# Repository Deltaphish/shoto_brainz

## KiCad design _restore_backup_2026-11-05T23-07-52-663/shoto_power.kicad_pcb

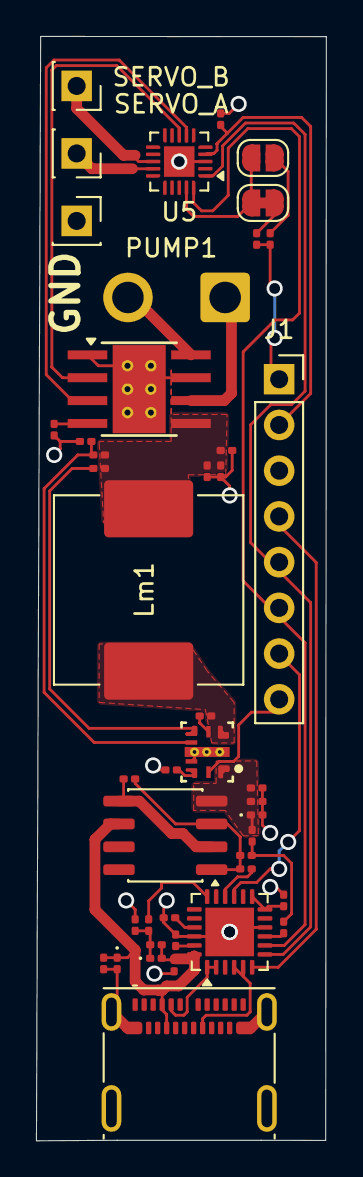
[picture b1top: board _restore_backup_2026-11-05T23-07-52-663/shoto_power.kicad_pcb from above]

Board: 2 copper layers, 16.1 x 61.4 mm, 44 parts (0 on the bottom side), 38 nets.

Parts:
C2: 4.7uf; C_0201_0603Metric
C3, C4, C5, C6: 1uf; C_0201_0603Metric
C7: 100nf; C_0201_0603Metric
C15: 47uF; C_0201_0603Metric
C16, C17: 0.1uF; C_0201_0603Metric
Cm_boot1: 100nF; C_0201_0603Metric
Cm_in1: 4.7uF; C_0201_0603Metric
Cm_inx1: 100nF; C_0201_0603Metric
Cm_out1: 100nF; C_0201_0603Metric
D1: D_Zener; D_0201_0603Metric
D2: VBUS TVS; D_0201_0603Metric
D3: VUSB TVS; D_0201_0603Metric
J1: Conn_01x08_Pin; PinSocket_1x08_P2.54mm_Vertical
J2: USB_C_Receptacle; USB_C_Receptacle_Molex_105450-0101
JP3: SolderJumper_2_Bridged; SolderJumper-2_P1.3mm_Bridged_RoundedPad1.0x1.5mm
JP4: SolderJumper_2_Open; SolderJumper-2_P1.3mm_Open_RoundedPad1.0x1.5mm
Lm1: 3.3uH; L_Vishay_IHLP-4040
PUMP1: Conn_01x02_Socket; SolderWire-1sqmm_1x02_P5.4mm_D1.4mm_OD2.7mm
Q3: Q_Dual_PMOS_G1S2G2D2S1D1; SO-8_3.9x4.9mm_P1.27mm
R3, R8, R20: 1k; R_0201_0603Metric
R4: 470; R_0201_0603Metric
R5, R9, R10: 100k; R_0201_0603Metric
R6: 22k; R_0201_0603Metric
R7: 100; R_0201_0603Metric
R11: 9.09k; R_0201_0603Metric
R18: 32k; R_0201_0603Metric
R19: 4.7k; R_0201_0603Metric
Rm_pg1: 100k; R_0201_0603Metric
Rm_rt1: 15.4k; R_0201_0603Metric
SERVO_A: Conn_01x01_Socket; PinSocket_1x01_P2.54mm_Vertical
SERVO_B: Conn_01x01_Socket; PinSocket_1x01_P2.54mm_Vertical
SERVO_GND1: Conn_01x01_Socket; PinSocket_1x01_P2.54mm_Vertical
U2: STUSB4500QTR; QFN-24-1EP_4x4mm_P0.5mm_EP2.7x2.7mm
U3: PLMR604303SRAKRQ1; RAK0009A-MFG
U5: ATtiny1616-M; VQFN-20-1EP_3x3mm_P0.4mm_EP1.7x1.7mm
U6: DRV8871DDA; Texas_HTSOP-8-1EP_3.9x4.9mm_P1.27mm_EP2.95x4.9mm_Mask2.4x3.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

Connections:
3V3: C17.1, J1.2, U5.4 (VCC)
/Motor Controller/12V: C15.1, C16.1, Cm_out1.2, Lm1.2, R10.1, Rm_pg1.2, U6.5 (VM)
/Motor Controller/M1: PUMP1.1, U6.6 (OUT1)
/Motor Controller/M2: PUMP1.2, U6.8 (OUT2)
/Motor Controller/SERVO_1: SERVO_A.1 (Pin_1_1), U5.14 (PB0)
/Motor Controller/SERVO_2: SERVO_B.1 (Pin_1_1), U5.13 (PB1)
/Motor PSU/VUSB: C7.1, Cm_in1.1, Cm_inx1.1, D3.1 (K), Q3.4 (D), U3.1 (VIN)
/USB PD Controller/CC1: J2.A5 (CC1), U2.1 (CC1DB), U2.2 (CC1)
/USB PD Controller/CC2: J2.B5 (CC2), U2.4 (CC2), U2.5 (CC2DB)
/USB PD Controller/VBUS_IN: C2.1, C6.1, D1.1 (K), D2.2 (A), J2.A4 (VBUS), J2.A9 (VBUS), J2.B4 (VBUS), J2.B9 (VBUS), Q3.6 (D), R4.2, U2.24 (VDD)
GND: C2.2, C3.2, C4.2, C5.2, C6.2, C15.2, C16.2, C17.2, Cm_in1.2, Cm_inx1.2, Cm_out1.1, D1.2 (A), D3.2 (A), J1.3, J2.A1 (GND), J2.A12 (GND), J2.B1 (GND), J2.B12 (GND), J2.SH (SHIELD), R9.2, R11.2, R18.2, Rm_rt1.1, SERVO_GND1.1 (Pin_1_1), U2.10 (GND), U2.22 (VSYS), U2.25 (GND), U3.2 (PGND), U3.7 (MODE_SYNC), U3.10, U3.11, U3.12, U5.3 (GND), U5.21 (GND), U6.1 (GND), U6.7 (GND), U6.9 (GND)
I2C SCL: J1.5, U2.7 (SCL), U5.1 (PA2)
I2C SDA: J1.6, U2.8 (SDA), U5.20 (PA1)
Motor_PSU_Enable: J1.8, U3.9 (EN)
unnamed: C7.2, R7.2, R8.2
unnamed: C3.1, D2.1 (K), R3.2, R4.1
unnamed: JP3.1 (A), JP4.1 (A), U5.19 (~RESET/PA0)
unnamed: JP3.2 (B), R19.1
unnamed: JP4.2 (B), R20.1
unnamed: Q3.1 (G), Q3.3 (G), R5.2, R6.1, R7.1
unnamed: Q3.2 (S), Q3.5 (S), R5.1
unnamed: R9.1, U2.12 (ADDR0), U2.13 (ADDR1)
unnamed: R8.1, U2.9 (DISCH)
unnamed: R6.2, U2.16 (VBUS_EN_SNK)
unnamed: R3.1, U2.18 (VBUS_VS_DISCH)
unnamed: C5.1, U2.21 (VREG_1V2)
unnamed: C4.1, U2.23 (VREG_2V7)
unnamed: Cm_boot1.1, U3.4 (BOOT)
unnamed: R10.2, R11.1, U3.6 (FB)
unnamed: Rm_pg1.1, U3.5 (PG)
unnamed: Rm_rt1.2, U3.8 (RT)
unnamed: Cm_boot1.2, Lm1.1, U3.3 (SW)
unnamed: U5.7 (PA6), U6.3 (IN1)
unnamed: U5.8 (PA7), U6.2 (IN2)
unnamed: R18.1, U6.4 (ILIM)
PROG: J1.1, R19.2, R20.2
USB PD GPIO: J1.7, U2.15 (GPIO)
USB PD RESET: J1.4, U2.6 (RESET)

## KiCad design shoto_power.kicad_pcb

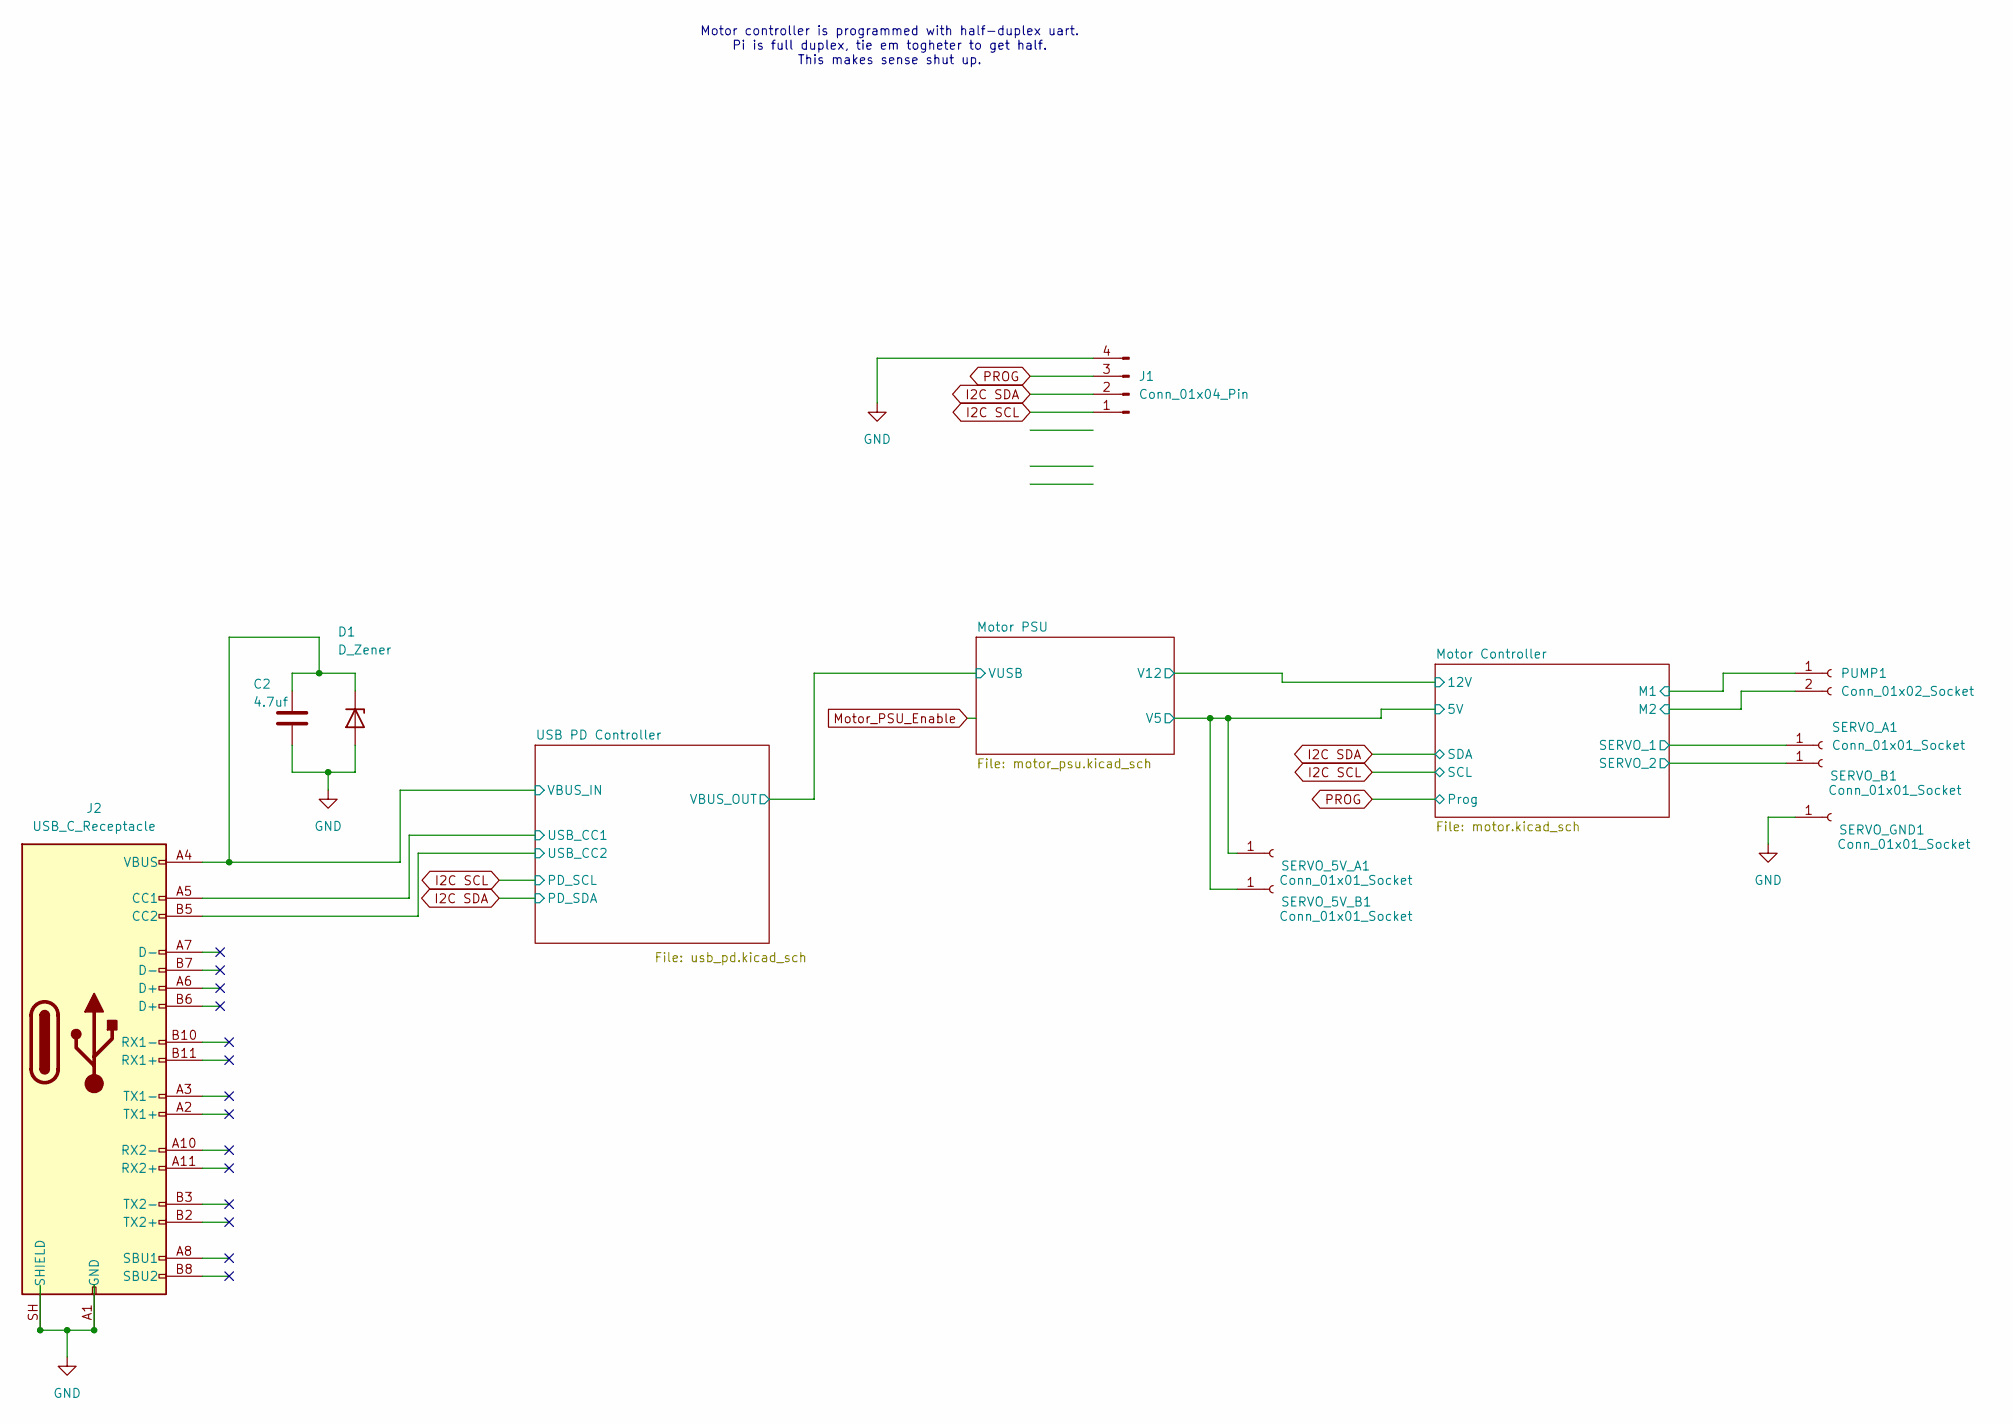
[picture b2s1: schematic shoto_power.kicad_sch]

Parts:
C2: 4.7uf; C_0603_1608Metric
D1: D_Zener; D_0201_0603Metric
J1: Conn_01x04_Pin; PinHeader_1x04_P2.54mm_Vertical
J2: USB_C_Receptacle; USB_C_Receptacle_Molex_105450-0101
PUMP1: Conn_01x02_Socket; SolderWire-1sqmm_1x02_P5.4mm_D1.4mm_OD2.7mm
SERVO_5V_A1, SERVO_5V_B1: Conn_01x01_Socket; PinSocket_1x01_P2.54mm_Vertical
SERVO_A1: Conn_01x01_Socket; PinSocket_1x01_P2.54mm_Vertical
SERVO_B1: Conn_01x01_Socket; PinSocket_1x01_P2.54mm_Vertical
SERVO_GND1: Conn_01x01_Socket; PinSocket_1x01_P2.54mm_Vertical

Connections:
/Motor Controller/5V: SERVO_5V_A1.1 (Pin_1_1), SERVO_5V_B1.1 (Pin_1_1); also elsewhere on the board
/Motor Controller/M1: PUMP1.1; also elsewhere on the board
/Motor Controller/M2: PUMP1.2; also elsewhere on the board
/Motor Controller/T2CH4: SERVO_B1.1 (Pin_1_1); also elsewhere on the board
/Motor PSU/VUSB: C2.1, D1.1 (K), J2.A4 (VBUS), J2.A9 (VBUS), J2.B4 (VBUS), J2.B9 (VBUS); also elsewhere on the board
/USB PD Controller/USB_CC1: J2.A5 (CC1); also elsewhere on the board
/USB PD Controller/USB_CC2: J2.B5 (CC2); also elsewhere on the board
GND: C2.2, D1.2 (A), J1.4, J2.A1 (GND), J2.A12 (GND), J2.B1 (GND), J2.B12 (GND), J2.SH (SHIELD), SERVO_GND1.1 (Pin_1_1); also elsewhere on the board
I2C SCL: J1.1; also elsewhere on the board
I2C SDA: J1.2; also elsewhere on the board
PROG: J1.3; also elsewhere on the board

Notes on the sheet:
Motor controller is programmed with half-duplex uart. Pi is full duplex, tie em togheter to get half. This makes sense shut up.

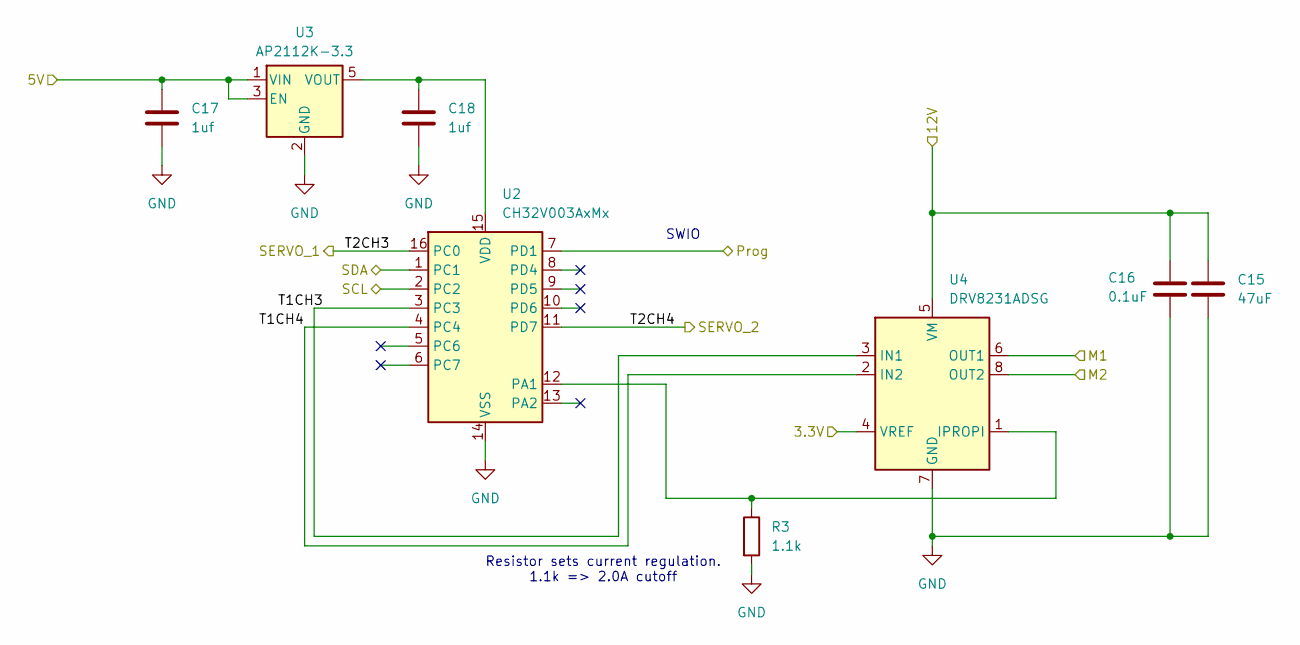
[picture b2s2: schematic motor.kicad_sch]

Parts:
C15: 47uF; C_Elec_6.3x5.4
C16: 0.1uF; C_0201_0603Metric
C17, C18: 1uf; C_0603_1608Metric
R3: 1.1k; R_0805_2012Metric
U2: CH32V003AxMx; STC_SOP-16_3.9x9.9mm_P1.27mm
U3: AP2112K-3.3; SOT-23-5
U4: DRV8231ADSG; Texas_DSG0008A_WSON-8-1EP_2x2mm_P0.5mm_EP0.9x1.6mm

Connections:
/Motor Controller/5V: C17.1, U3.1 (VIN), U3.3 (EN); also elsewhere on the board
/Motor Controller/12V: C15.1, C16.1, U4.5 (VM); also elsewhere on the board
/Motor Controller/M1: U4.6 (OUT1); also elsewhere on the board
/Motor Controller/M2: U4.8 (OUT2); also elsewhere on the board
/Motor Controller/T1CH3: U2.3 (PC3), U4.3 (IN1)
/Motor Controller/T1CH4: U2.4 (PC4), U4.2 (IN2)
/Motor Controller/T2CH3: U2.16 (PC0); also elsewhere on the board
/Motor Controller/T2CH4: U2.11 (PD7); also elsewhere on the board
GND: C15.2, C16.2, C17.2, C18.2, R3.2, U2.14 (VSS), U3.2 (GND), U4.7 (GND), U4.9 (GND); also elsewhere on the board
I2C SCL: U2.2 (PC2); also elsewhere on the board
I2C SDA: U2.1 (PC1); also elsewhere on the board
unnamed: R3.1, U2.12 (PA1), U4.1 (IPROPI)
PROG: U2.7 (PD1); also elsewhere on the board

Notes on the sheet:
Resistor sets current regulation. 1.1k => 2.0A cutoff
SWIO

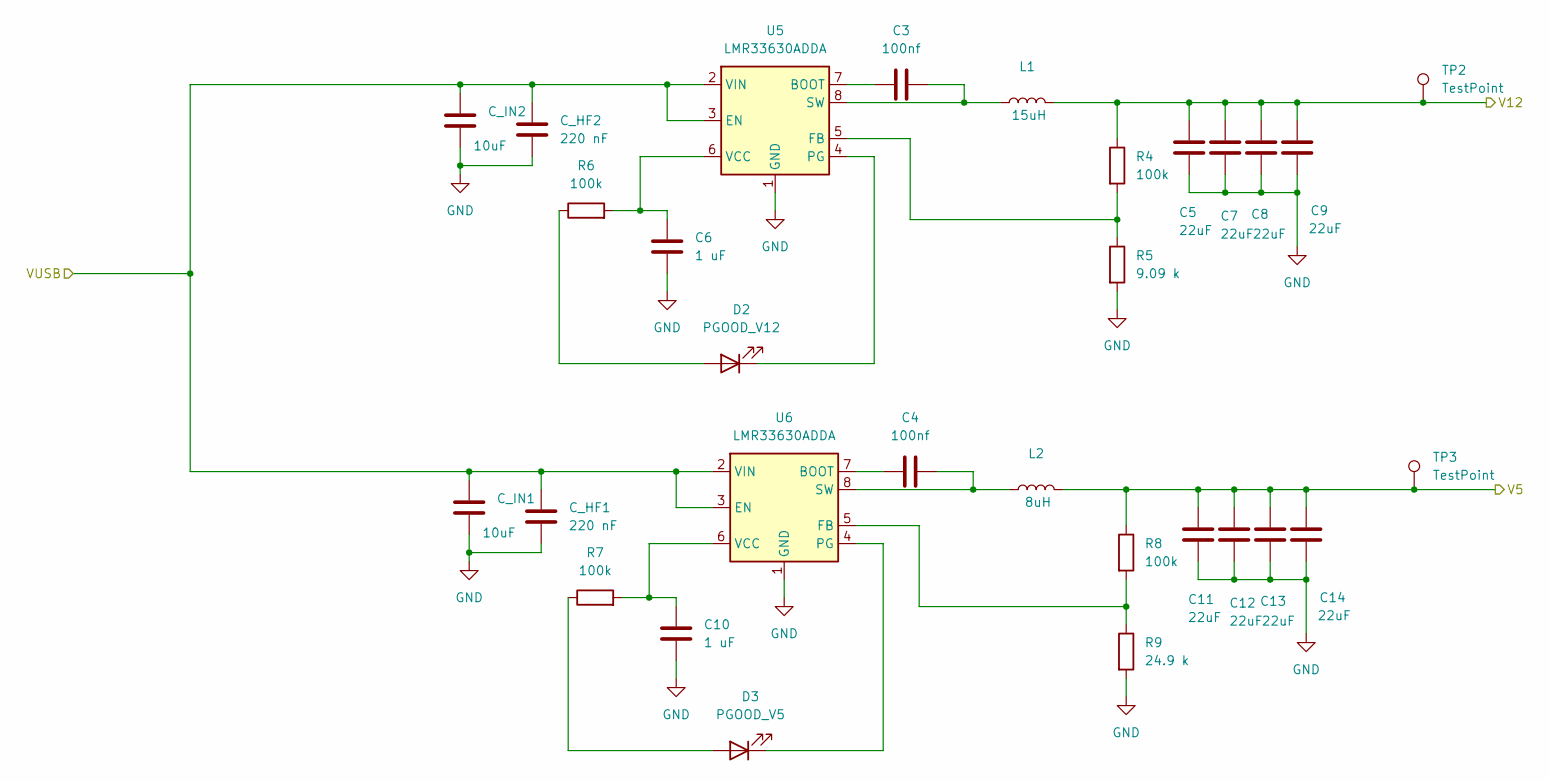
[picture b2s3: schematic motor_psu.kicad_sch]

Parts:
C3, C4: 100nf; C_0603_1608Metric
C5, C7, C8, C9, C11, C12, C13, C14: 22uF; C_1206_3216Metric
C6, C10: 1 uF; C_0603_1608Metric
C_HF1, C_HF2: 220 nF; C_0603_1608Metric
C_IN1, C_IN2: 10uF; C_1206_3216Metric
D2: PGOOD_V12; LED_0603_1608Metric
D3: PGOOD_V5; LED_0603_1608Metric
L1: 15uH; SMDRH104R
L2: 8uH; SER1360
R4, R6, R7, R8: 100k; R_0805_2012Metric
R5: 9.09 k; R_0805_2012Metric
R9: 24.9 k; R_0805_2012Metric
TP2, TP3: TestPoint; TestPoint_Pad_1.5x1.5mm
U5, U6: LMR33630ADDA; Texas_HSOP-8-1EP_3.9x4.9mm_P1.27mm_ThermalVias

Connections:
/Motor Controller/5V: C11.1, C12.1, C13.1, C14.1, L2.2, R8.1, TP3.1; also elsewhere on the board
/Motor Controller/12V: C5.1, C7.1, C8.1, C9.1, L1.2, R4.1, TP2.1 (1_1); also elsewhere on the board
/Motor PSU/VUSB: C_HF1.2, C_HF2.2, C_IN1.2, C_IN2.2, U5.2 (VIN), U5.3 (EN), U6.2 (VIN), U6.3 (EN); also elsewhere on the board
GND: C5.2, C6.2, C7.2, C8.2, C9.2, C10.2, C11.2, C12.2, C13.2, C14.2, C_HF1.1, C_HF2.1, C_IN1.1, C_IN2.1, R5.2, R9.2, U5.1 (GND), U5.9 (GND), U6.1 (GND), U6.9 (GND); also elsewhere on the board
unnamed: D2.2 (A), R6.1
unnamed: D2.1 (K), U5.4 (PG)
unnamed: D3.2 (A), R7.1
unnamed: D3.1 (K), U6.4 (PG)
unnamed: C3.1, U5.7 (BOOT)
unnamed: R4.2, R5.1, U5.5 (FB)
unnamed: C3.2, L1.1, U5.8 (SW)
unnamed: C6.1, R6.2, U5.6 (VCC)
unnamed: C4.1, U6.7 (BOOT)
unnamed: R8.2, R9.1, U6.5 (FB)
unnamed: C4.2, L2.1, U6.8 (SW)
unnamed: C10.1, R7.2, U6.6 (VCC)

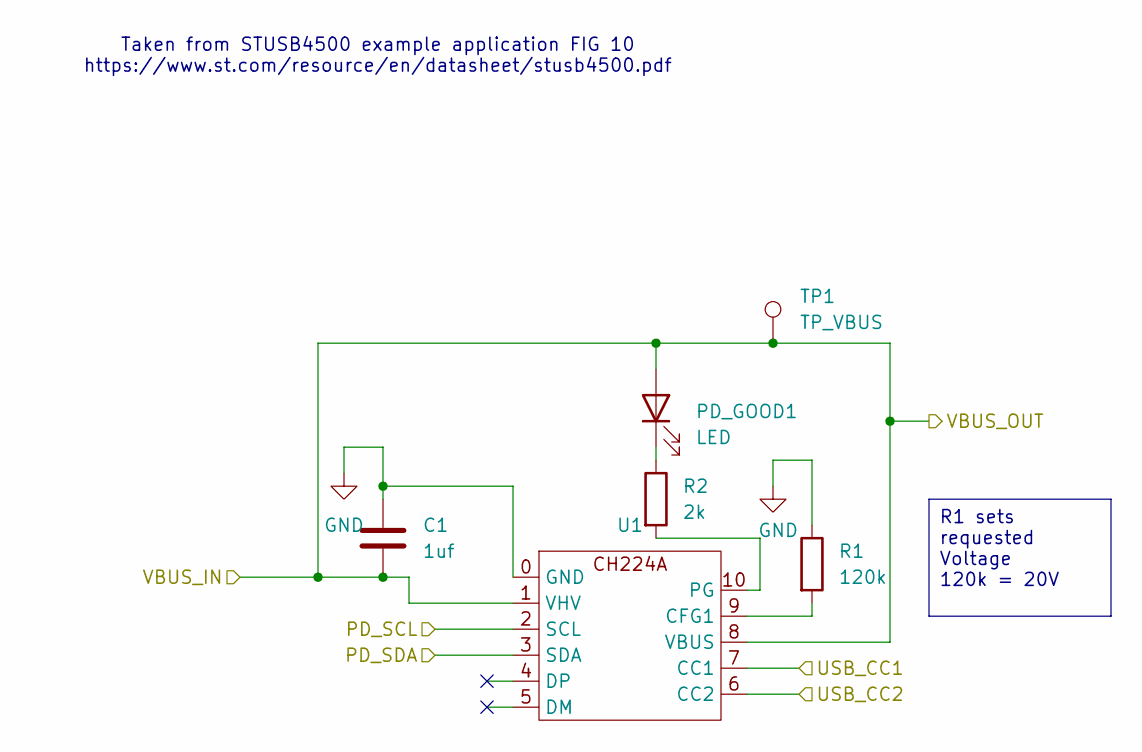
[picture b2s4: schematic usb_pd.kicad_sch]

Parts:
C1: 1uf; C_0603_1608Metric
PD_GOOD1: LED; LED_0603_1608Metric
R1: 120k; R_0805_2012Metric
R2: 2k; R_0805_2012Metric
TP1: TP_VBUS; TestPoint_Pad_D2.5mm
U1: CH224A

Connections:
/Motor PSU/VUSB: C1.2, PD_GOOD1.2 (A), TP1.1 (1_1), U1.1 (VHV), U1.8 (VBUS); also elsewhere on the board
/USB PD Controller/USB_CC1: U1.7 (CC1); also elsewhere on the board
/USB PD Controller/USB_CC2: U1.6 (CC2); also elsewhere on the board
GND: C1.1, R1.1, U1.0 (GND); also elsewhere on the board
I2C SCL: U1.2 (SCL); also elsewhere on the board
I2C SDA: U1.3 (SDA); also elsewhere on the board
unnamed: PD_GOOD1.1 (K), R2.1
unnamed: R1.2, U1.9 (CFG1)
unnamed: R2.2, U1.10 (PG)

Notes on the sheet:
Taken from STUSB4500 example application FIG 10 https://www.st.com/resource/en/datasheet/stusb4500.pdf
R1 sets requested Voltage 120k = 20V

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
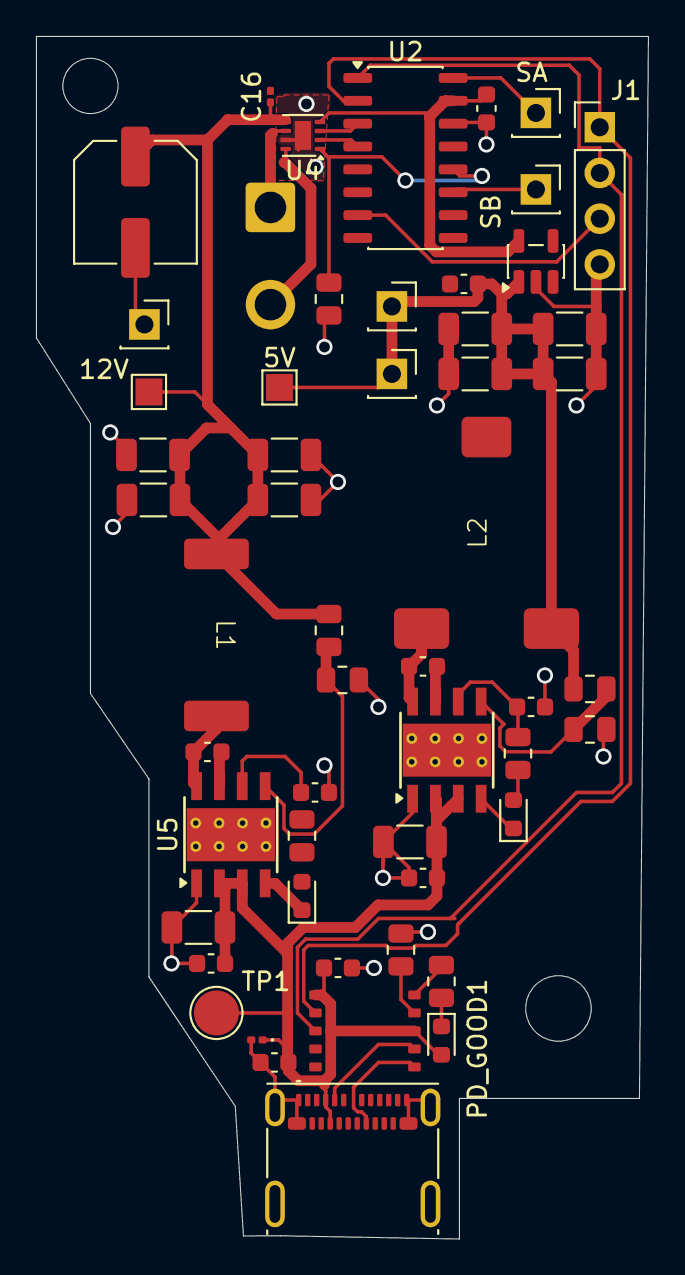
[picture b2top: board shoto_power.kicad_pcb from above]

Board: 2 copper layers, 34.0 x 66.8 mm, 54 parts (0 on the bottom side), 32 nets.

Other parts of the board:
5V: TestPoint; TestPoint_Pad_1.5x1.5mm
SA: Conn_01x01_Socket; PinSocket_1x01_P2.54mm_Vertical

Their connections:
/Motor Controller/5V: 5V.1 (1_1); also elsewhere on the board
/Motor Controller/T2CH3: SA.1 (Pin_1_1); also elsewhere on the board
